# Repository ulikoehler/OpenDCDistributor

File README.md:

# OpenDCDistributor
Open-hardware PCB to distribute DC 12V power to 12V / 5V / 9V &amp; 24V consumers

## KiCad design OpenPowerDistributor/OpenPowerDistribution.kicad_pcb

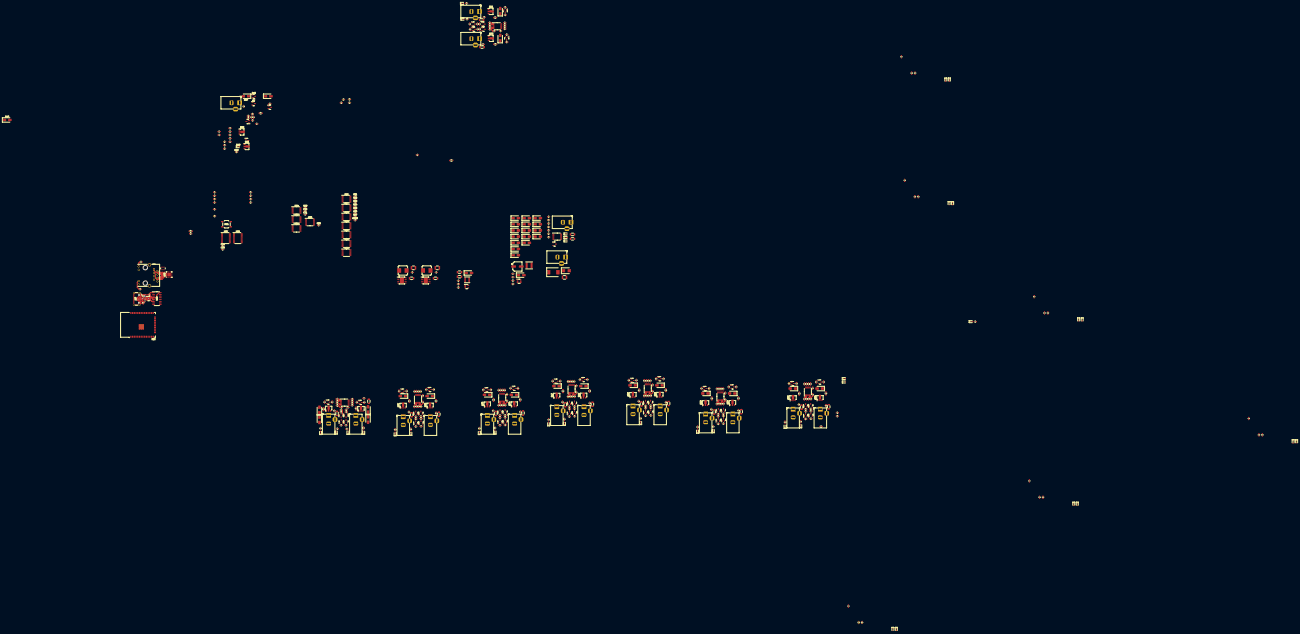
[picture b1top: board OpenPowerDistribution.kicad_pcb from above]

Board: 2 copper layers, 537 parts (0 on the bottom side), 340 nets.

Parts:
C1, C4, C49: 47uF 16V; C_1210_3225Metric
C2, C9, C11, C47: 10uF 50V; C_1206_3216Metric
C3, C12, C13, C16, C17, C18, C21, C22, C23, C26, C27, C28, C31, C32, C33, C36, C37, C38, C41, C42, C43, C46, C48, C51, C52, C55, C56, C57, C60, C72, C73: 100nF 16V; C_0603_1608Metric
C6, C61, C62, C63, C64, C65, C66, C67, C68, C69, C70, C71, C74, C75, C77, C78, C81: 100nF; C_0603_1608Metric
C7: 100pF; C_0603_1608Metric
C8: 47uF 35V; CP_Elec_6.3x5.4
C10, C14, C15, C19, C20, C24, C25, C29, C30, C34, C35, C39, C40, C44, C45, C53, C54, C58, C59: NA; C_0603_1608Metric
C76, C79: 1uF 6.3V; C_0603_1608Metric
D1: SS84C; D_SMC
D2: SMBJ12A; D_SMB
D3: SMAJ3.3A; D_SMA
D4, D7, D8, D15, D15#2, D16, D23, D24, D31, D32, D39, D40, D47, D48, D55, D56, D63, D64, D89, D90: SS36(F); D_SMA
D5, D6, D13, D14, D21, D22, D29, D30, D37, D38, D45, D46, D53, D54, D61, D62, D87, D88: AZ23C16; SOT-23
D9, D11, D17, D19, D25, D27, D33, D35, D41, D43, D49, D51, D57, D59, D65, D67, D91, D93: Red; LED_0603_1608Metric
D10, D12, D18, D20, D26, D28, D34, D36, D42, D44, D50, D52, D58, D60, D66, D68, D92, D94: Green; LED_0603_1608Metric
D69, D70, D71, D72, D73, D74: SMAJ5.0A; D_SMA
D75, D76: SMAJ24A; D_SMA
D77, D78, D79, D80, D81, D82: SMAJ12A; D_SMA
D83, D84, D85, D86: SMAJ9.0A; D_SMA
FB1, FB2, FB3, FB4, FB5, FB6, FB7, FB8, FB9, FB10, FB11, FB12, FB13, FB14, FB15, FB16, FB17, FB18: 220R@100MHz 3A; L_0805_2012Metric
FB19: 200mA 1kR; L_0805_2012Metric
J1, J2, J3, J4, J5, J6, J7, J8, J9, J10, J11, J12, J13, J14, J15, J16, J17, J18, J19: Barrel_Jack; BarrelJack_Horizontal
J20: USB_C_Receptacle_USB2.0; USB_C_Receptacle_HCTL_HC-TYPE-C-16P-01A
J22: RJ45_Hanrun_HR911105A_Horizontal
L1, L4: 3.3uH; L_Bourns_SRP7028A_7.3x6.6mm
L2: 10uH 2A; L_Taiyo-Yuden_NR-50xx
L3: 4.7uH 2A; L_Abracon_ASPI-4030S
Q1, Q2, Q3, Q4, Q7, Q8, Q9, Q10, Q13, Q14, Q15, Q16, Q19, Q20, Q21, Q22, Q25, Q26, Q27, Q28, Q31, Q32, Q33, Q34, Q37, Q38, Q39, Q40, Q43, Q44, Q45, Q46, Q49, Q50, Q51, Q52: BC847; SOT-23
Q5, Q6, Q11, Q12, Q17, Q18, Q23, Q24, Q29, Q30, Q35, Q36, Q41, Q42, Q47, Q48, Q53, Q54: HL20N04; SOT-89-3
R1, R5, R7, R8, R19, R20, R31, R32, R43, R44, R55, R56, R67, R68, R79, R80, R91, R92, R103, R104, R115, R116, R127, R128, R139, R140, R151, R152, R163, R164, R175, R177, R178, R189, R190, R201, R202, R213, R214: 390k; R_0603_1608Metric
R2, R176: 49.9k; R_0603_1608Metric
R3, R225: 220k; R_0603_1608Metric
R4: 68k; R_0603_1608Metric
R6, R9, R10, R33, R34, R57, R58, R81, R82, R105, R106, R129, R130, R153, R154, R179, R180, R203, R204: 15k; R_0603_1608Metric
R11, R12, R25, R26, R35, R36, R49, R50, R59, R60, R73, R74, R83, R84, R97, R98, R107, R108, R121, R122, R131, R132, R145, R146, R155, R156, R169, R170, R181, R182, R195, R196, R205, R206, R219, R220: 100k; R_0603_1608Metric
R13, R14, R15, R17, R37, R38, R39, R41, R61, R62, R63, R65, R85, R86, R87, R89, R109, R110, R111, R113, R133, R134, R135, R137, R157, R158, R159, R161, R183, R184, R185, R187, R207, R208, R209, R211: 1M; R_0603_1608Metric
R16, R18, R40, R42, R64, R66, R88, R90, R112, R114, R136, R138, R160, R162, R186, R188, R210, R212: 33k; R_0603_1608Metric
R21, R22, R45, R46, R69, R70, R93, R94, R117, R118, R141, R142, R165, R166, R191, R192, R215, R216, R226, R229, R230: 10k; R_0603_1608Metric
R23, R24, R47, R48, R71, R72, R95, R96, R119, R120, R143, R144, R167, R168, R193, R194, R217, R218: 33mR; R_1206_3216Metric
R27, R28, R29, R30, R51, R52, R53, R54, R75, R76, R77, R78, R99, R100, R101, R102, R123, R124, R125, R126, R147, R148, R149, R150, R171, R172, R173, R174, R197, R198, R199, R200, R221, R222, R223, R224: 150R; R_0603_1608Metric
R227, R228: 5.1k; R_0603_1608Metric
R231, R233: 12.1k; R_0603_1608Metric
R232, R234: 270R; R_0603_1608Metric
RN1: 49.9R; R_Array_Concave_4x0603
SW1: RST; SW_SPST_TL3342
U1, U13: TPS565208DDA; Texas_HSOP-8-1EP_3.9x4.9mm_P1.27mm
U2: AP63200WU; TSOT-23-6
U3: LGS6302; SOT-23-5
U4, U5, U6, U7, U8, U9, U10, U11, U12: LM324; TSSOP-14_4.4x5mm_P0.65mm
U14: USBLC6-2SC6; SOT-23-6
U15: ESP32-WROOM-32; ESP32-WROOM-32D
U16, U17, U18, U19, U20, U21, U22: 74HCT595; TSSOP-16_4.4x5mm_P0.65mm
U23, U24, U25, U26: 74HC165; TSSOP-16_4.4x5mm_P0.65mm
U27, U28: CD4067BMT/TR; TSSOP-24_4.4x7.8mm_P0.65mm
U29: CH340C; SOIC-16_3.9x9.9mm_P1.27mm
U30: LAN8720A; QFN-24-1EP_4x4mm_P0.5mm_EP2.6x2.6mm

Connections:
+3.3V: C7.1, C8.1, C61.2, C62.2, C63.2, C64.2, C65.2, C66.2, C67.2, C68.2, C69.2, C70.2, C71.2, C74.2, C75.1, D3.1 (A1), FB19.2, L2.2, R3.1, R225.1, R226.1, R229.1, R232.2, U15.2 (VDD), U16.10 (~SRCLR), U16.16 (VCC), U17.10 (~SRCLR), U17.16 (VCC), U18.10 (~SRCLR), U18.16 (VCC), U19.10 (~SRCLR), U19.16 (VCC), U20.10 (~SRCLR), U20.16 (VCC), U21.10 (~SRCLR), U21.16 (VCC), U22.10 (~SRCLR), U22.16 (VCC), U23.16 (VCC), U24.16 (VCC), U25.16 (VCC), U26.16 (VCC), U29.4 (V3), U29.16 (VCC), U30.9 (VDDIO)
+3.3VPHY: C77.2, C78.2, C79.2, C81.2, FB19.1, J22.4 (TCT), J22.5 (RCT), RN1.5 (R4.2), RN1.6 (R3.2), RN1.7 (R2.2), RN1.8 (R1.2), U30.1 (VDD2A), U30.19 (VDD1A)
+3V3: C72.1, C73.1, R9.1, R10.1, R27.2, R28.2, R29.2, R30.2, R33.1, R34.1, R51.2, R52.2, R53.2, R54.2, R57.1, R58.1, R75.2, R76.2, R77.2, R78.2, R81.1, R82.1, R99.2, R100.2, R101.2, R102.2, R105.1, R106.1, R123.2, R124.2, R125.2, R126.2, R129.1, R130.1, R147.2, R148.2, R149.2, R150.2, R153.1, R154.1, R171.2, R172.2, R173.2, R174.2, R179.1, R180.1, R197.2, R198.2, R199.2, R200.2, R203.1, R204.1, R221.2, R222.2, R223.2, R224.2, U27.24 (VCC), U28.24 (VCC)
+5V: C4.2, D7.2 (A), D8.2 (A), D15.2 (A), D15#2.2 (A), D16.2 (A), D23.2 (A), D24.2 (A), L1.2, R1.1, U3.4 (EN)
+9V: C49.2, D63.2 (A), D64.2 (A), D89.2 (A), D90.2 (A), L4.2, R175.1
+12V: C1.2, C9.2, C16.1, C21.1, C26.1, C31.1, C36.1, C41.1, C46.1, C55.1, C60.1, D1.1 (K), D2.1 (A1), D31.2 (A), D32.2 (A), D39.2 (A), D40.2 (A), D47.2 (A), D48.2 (A), L3.1, U1.1 (EN), U1.8 (VIN), U2.2 (EN), U2.3 (IN), U3.5 (IN), U4.4 (V+), U5.4 (V+), U6.4 (V+), U7.4 (V+), U8.4 (V+), U9.4 (V+), U10.4 (V+), U11.4 (V+), U12.4 (V+), U13.1 (EN), U13.8 (VIN)
+24V: D55.2 (A), D56.2 (A)
+30V: C10.1, C11.2, D4.1 (K), R5.1, R15.1, R17.1, R39.1, R41.1, R63.1, R65.1, R87.1, R89.1, R111.1, R113.1, R135.1, R137.1, R159.1, R161.1, R185.1, R187.1, R209.1, R211.1
/Analog multiplexer/AMUX-Out: U27.1 (COM), U28.1 (COM)
/Analog multiplexer/AMUX.A0: U27.10 (S0), U28.10 (S0)
/Analog multiplexer/AMUX.A1: U27.11 (S1), U28.11 (S1)
/Analog multiplexer/AMUX.A2: U27.14 (S2), U28.14 (S2)
/Analog multiplexer/AMUX.A3: U27.13 (S3), U28.13 (S3)
/DC Output channels/5V output #1/O1+: D5.2 (K), D69.1 (A1), J2.1, Q5.3 (S), R25.1
/DC Output channels/5V output #1/O1-: D69.2 (A2), J2.2, R23.1, R25.2, U4.5 (+)
/DC Output channels/5V output #1/O2+: D6.2 (K), D70.1 (A1), J3.1, Q6.3 (S), R26.1
/DC Output channels/5V output #1/O2-: D70.2 (A2), J3.2, R24.1, R26.2, U4.12 (+)
/DC Output channels/5V output #2/O1+: D13.2 (K), D71.1 (A1), J4.1, Q11.3 (S), R49.1
/DC Output channels/5V output #2/O1-: D71.2 (A2), J4.2, R47.1, R49.2, U8.5 (+)
/DC Output channels/5V output #2/O2+: D14.2 (K), D72.1 (A1), J5.1, Q12.3 (S), R50.1
/DC Output channels/5V output #2/O2-: D72.2 (A2), J5.2, R48.1, R50.2, U8.12 (+)
/DC Output channels/5V output #3/O1+: D21.2 (K), D73.1 (A1), J6.1, Q17.3 (S), R73.1
/DC Output channels/5V output #3/O1-: D73.2 (A2), J6.2, R71.1, R73.2, U9.5 (+)
/DC Output channels/5V output #3/O2+: D22.2 (K), D74.1 (A1), J7.1, Q18.3 (S), R74.1
/DC Output channels/5V output #3/O2-: D74.2 (A2), J7.2, R72.1, R74.2, U9.12 (+)
/DC Output channels/9V output #1/O1+: D61.2 (K), D83.1 (A1), J16.1, Q47.3 (S), R195.1
/DC Output channels/9V output #1/O1-: D83.2 (A2), J16.2, R193.1, R195.2, U6.5 (+)
/DC Output channels/9V output #1/O2+: D62.2 (K), D84.1 (A1), J17.1, Q48.3 (S), R196.1
/DC Output channels/9V output #1/O2-: D84.2 (A2), J17.2, R194.1, R196.2, U6.12 (+)
/DC Output channels/9V output #2/O1+: D85.1 (A1), D87.2 (K), J18.1, Q53.3 (S), R219.1
/DC Output channels/9V output #2/O1-: D85.2 (A2), J18.2, R217.1, R219.2, U7.5 (+)
/DC Output channels/9V output #2/O2+: D86.1 (A1), D88.2 (K), J19.1, Q54.3 (S), R220.1
/DC Output channels/9V output #2/O2-: D86.2 (A2), J19.2, R218.1, R220.2, U7.12 (+)
/DC Output channels/12V output #1/O1+: D29.2 (K), D77.1 (A1), J8.1, Q23.3 (S), R97.1
/DC Output channels/12V output #1/O1-: D77.2 (A2), J8.2, R95.1, R97.2, U10.5 (+)
/DC Output channels/12V output #1/O2+: D30.2 (K), D78.1 (A1), J9.1, Q24.3 (S), R98.1
/DC Output channels/12V output #1/O2-: D78.2 (A2), J9.2, R96.1, R98.2, U10.12 (+)
/DC Output channels/12V output #2/O1+: D37.2 (K), D79.1 (A1), J10.1, Q29.3 (S), R121.1
/DC Output channels/12V output #2/O1-: D79.2 (A2), J10.2, R119.1, R121.2, U11.5 (+)
/DC Output channels/12V output #2/O2+: D38.2 (K), D80.1 (A1), J11.1, Q30.3 (S), R122.1
/DC Output channels/12V output #2/O2-: D80.2 (A2), J11.2, R120.1, R122.2, U11.12 (+)
/DC Output channels/12V output #3/O1+: D45.2 (K), D81.1 (A1), J12.1, Q35.3 (S), R145.1
/DC Output channels/12V output #3/O1-: D81.2 (A2), J12.2, R143.1, R145.2, U5.5 (+)
/DC Output channels/12V output #3/O2+: D46.2 (K), D82.1 (A1), J13.1, Q36.3 (S), R146.1
/DC Output channels/12V output #3/O2-: D82.2 (A2), J13.2, R144.1, R146.2, U5.12 (+)
/DC Output channels/24V output #1/O1+: D53.2 (K), D75.1 (A1), J14.1, Q41.3 (S), R169.1
/DC Output channels/24V output #1/O1-: D75.2 (A2), J14.2, R167.1, R169.2, U12.5 (+)
/DC Output channels/24V output #1/O2+: D54.2 (K), D76.1 (A1), J15.1, Q42.3 (S), R170.1
/DC Output channels/24V output #1/O2-: D76.2 (A2), J15.2, R168.1, R170.2, U12.12 (+)
/DC Output channels/A_{In}1: C14.2, R19.1, U4.3 (+), U4.7
/DC Output channels/A_{In}2: C15.2, R20.1, U4.9 (-), U4.14
/DC Output channels/A_{In}3: C19.2, R43.1, U8.3 (+), U8.7
/DC Output channels/A_{In}4: C20.2, R44.1, U8.9 (-), U8.14
/DC Output channels/A_{In}5: C24.2, R67.1, U9.3 (+), U9.7
/DC Output channels/A_{In}6: C25.2, R68.1, U9.9 (-), U9.14
/DC Output channels/A_{In}7: C44.2, R163.1, U12.3 (+), U12.7
/DC Output channels/A_{In}8: C45.2, R164.1, U12.9 (-), U12.14
/DC Output channels/A_{In}9: C29.2, R91.1, U10.3 (+), U10.7
/DC Output channels/A_{In}10: C30.2, R92.1, U10.9 (-), U10.14
/DC Output channels/A_{In}11: C34.2, R115.1, U11.3 (+), U11.7
/DC Output channels/A_{In}12: C35.2, R116.1, U11.9 (-), U11.14
/DC Output channels/A_{In}13: C39.2, R139.1, U5.3 (+), U5.7
/DC Output channels/A_{In}14: C40.2, R140.1, U5.9 (-), U5.14
/DC Output channels/A_{In}15: C53.2, R189.1, U6.3 (+), U6.7
/DC Output channels/A_{In}16: C54.2, R190.1, U6.9 (-), U6.14
/DC Output channels/A_{In}17: C58.2, R213.1, U7.3 (+), U7.7
/DC Output channels/A_{In}18: C59.2, R214.1, U7.9 (-), U7.14
/DC Output channels/D_{In}1: Q1.3 (C), R9.2, U23.12 (D1)
/DC Output channels/D_{In}2: Q2.3 (C), R10.2, U23.13 (D2)
/DC Output channels/D_{In}3: Q7.3 (C), R33.2, U23.14 (D3)
/DC Output channels/D_{In}4: Q8.3 (C), R34.2, U23.3 (D4)
/DC Output channels/D_{In}5: Q13.3 (C), R57.2, U23.4 (D5)
/DC Output channels/D_{In}6: Q14.3 (C), R58.2, U23.5 (D6)
/DC Output channels/D_{In}7: Q37.3 (C), R153.2, U23.6 (D7)
/DC Output channels/D_{In}8: Q38.3 (C), R154.2, U24.11 (D0), U25.11 (D0)
/DC Output channels/D_{In}9: Q19.3 (C), R81.2, U24.12 (D1), U25.12 (D1)
/DC Output channels/D_{In}10: Q20.3 (C), R82.2, U24.13 (D2), U25.13 (D2)
/DC Output channels/D_{In}11: Q25.3 (C), R105.2, U24.14 (D3), U25.14 (D3)
/DC Output channels/D_{In}12: Q26.3 (C), R106.2, U24.3 (D4), U25.3 (D4)
/DC Output channels/D_{In}13: Q31.3 (C), R129.2, U24.4 (D5), U25.4 (D5)
/DC Output channels/D_{In}14: Q32.3 (C), R130.2, U24.5 (D6), U25.5 (D6)
/DC Output channels/D_{In}15: Q43.3 (C), R179.2, U24.6 (D7), U25.6 (D7)
/DC Output channels/D_{In}16: Q44.3 (C), R180.2, U26.11 (D0)
/DC Output channels/D_{In}17: Q49.3 (C), R203.2, U26.12 (D1)
/DC Output channels/D_{In}18: Q50.3 (C), R204.2, U26.13 (D2)
/Input multiplexer/SCLK: U16.11 (SRCLK), U17.11 (SRCLK), U18.11 (SRCLK), U19.11 (SRCLK), U20.11 (SRCLK), U21.11 (SRCLK), U22.11 (SRCLK), U23.2 (CP), U24.2 (CP), U25.2 (CP), U26.2 (CP)
/Input multiplexer/~LOAD: U16.12 (RCLK), U17.12 (RCLK), U18.12 (RCLK), U19.12 (RCLK), U20.12 (RCLK), U21.12 (RCLK), U22.12 (RCLK), U23.1 (~PL), U24.1 (~PL), U25.1 (~PL), U26.1 (~PL)
/MCU/DO4: R231.1, U15.14 (IO12)
/MCU/ESP32-RMII-CRSDV: U15.12 (IO27), U30.11 (CRS_DV/MODE2)
/MCU/ESP32-RMII-MDC: U15.37 (IO23), U30.13 (MDC)
/MCU/ESP32-RMII-MDIO: U15.30 (IO18), U30.12 (MDIO)
/MCU/ESP32-RMII-REFCLKOUT: U15.28 (IO17), U30.5 (XTAL1/CLKIN)
/MCU/ESP32-RMII-RXD0: U15.10 (IO25), U30.8 (RXD0/MODE0)
/MCU/ESP32-RMII-RXD1: U15.11 (IO26), U30.7 (RXD1/MODE1)
/MCU/ESP32-RMII-TX-EN: U15.33 (IO21), U30.16 (TXEN)
/MCU/ESP32-RMII-TXD0: U15.31 (IO19), U30.17 (TXD0)
/MCU/ESP32-RMII-TXD1: U15.36 (IO22), U30.18 (TXD1)
/MCU/Ethernet/1.2VPHY: C76.2, U30.6 (VDDCR)
/MCU/Ethernet/LED-Green: J22.10, U30.2 (LED2/nINTSEL)
/MCU/Ethernet/LED-Yellow: J22.12, U30.3 (LED1/REGOFF)
/MCU/Ethernet/PHY-RXN: J22.6 (RD-), RN1.4 (R4.1), U30.22 (RXN)
/MCU/Ethernet/PHY-RXP: J22.3 (RD+), RN1.3 (R3.1), U30.23 (RXP)
/MCU/Ethernet/PHY-TXN: J22.2 (TD-), RN1.2 (R2.1), U30.20 (TXN)
/MCU/Ethernet/PHY-TXP: J22.1 (TD+), RN1.1 (R1.1), U30.21 (TXP)
/Output multiplexer/~OE: R225.2, U16.13 (~OE), U17.13 (~OE), U18.13 (~OE), U19.13 (~OE), U20.13 (~OE), U21.13 (~OE), U22.13 (~OE)
/USB/USB-D+: J20.A6 (D+), J20.B6 (D+), U14.1 (I/O1), U14.6 (I/O1), U29.5 (UD+)
/USB/USB-D-: J20.A7 (D-), J20.B7 (D-), U14.3 (I/O2), U14.4 (I/O2), U29.6 (UD-)
ESP32-BOOT: R229.2, U15.25 (IO0), U29.14 (~RTS)
ESP32-UART-RX: U15.34 (RXD0/IO3), U29.2 (TXD)
ESP32-UART-TX: U15.35 (TXD0/IO1), U29.3 (RXD)
ESP32-~RST: R226.2, SW1.2, U15.3 (EN), U29.13 (~DTR), U30.15 (RST)
GND: C1.1, C2.1, C4.1, C8.2, C9.1, C11.1, C16.2, C21.2, C26.2, C31.2, C36.2, C41.2, C46.2, C47.1, C49.1, C55.2, C60.2, C61.1, C62.1, C63.1, C64.1, C65.1, C66.1, C67.1, C68.1, C69.1, C70.1, C71.1, C72.2, C73.2, C74.1, C75.2, C76.1, C77.1, C78.1, C79.1, C81.1, D2.2 (A2), D3.2 (A2), J1.2, J20.A1 (GND), J20.A12 (GND), J20.B1 (GND), J20.B12 (GND), J20.S1 (SHIELD), J22.8, J22.SH, Q1.2 (E), Q2.2 (E), Q3.2 (E), Q4.2 (E), Q7.2 (E), Q8.2 (E), Q9.2 (E), Q10.2 (E), Q13.2 (E), Q14.2 (E), Q15.2 (E), Q16.2 (E), Q19.2 (E), Q20.2 (E), Q21.2 (E), Q22.2 (E), Q25.2 (E), Q26.2 (E), Q27.2 (E), Q28.2 (E), Q31.2 (E), Q32.2 (E), Q33.2 (E), Q34.2 (E), Q37.2 (E), Q38.2 (E), Q39.2 (E), Q40.2 (E), Q43.2 (E), Q44.2 (E), Q45.2 (E), Q46.2 (E), Q49.2 (E), Q50.2 (E), Q51.2 (E), Q52.2 (E), R2.2, R4.2, R6.2, R21.1, R22.1, R23.2, R24.2, R45.1, R46.1, R47.2, R48.2, R69.1, R70.1, R71.2, R72.2, R93.1, R94.1, R95.2, R96.2, R117.1, R118.1, R119.2, R120.2, R141.1, R142.1, R143.2, R144.2, R165.1, R166.1, R167.2, R168.2, R176.2, R191.1, R192.1, R193.2, R194.2, R215.1, R216.1, R217.2, R218.2, R227.1, R228.1, R230.1, R231.2, R233.2, R234.2, SW1.1, U1.5 (GND), U1.9 (EP), U2.4 (GND), U3.2 (GND), U4.11 (V-), U5.11 (V-), U6.11 (V-), U7.11 (V-), U8.11 (V-), U9.11 (V-), U10.11 (V-), U11.11 (V-), U12.11 (V-), U13.5 (GND), U13.9 (EP), U14.2 (GND), U15.1 (GND), U15.15 (GND), U15.38 (GND), U15.39 (GND), U16.8 (GND), U17.8 (GND), U18.8 (GND), U19.8 (GND), U20.8 (GND), U21.8 (GND), U22.8 (GND), U23.8 (GND), U23.15 (~CE), U24.8 (GND), U24.15 (~CE), U25.8 (GND), U25.15 (~CE), U26.8 (GND), U26.15 (~CE), U27.12 (GND), U28.12 (GND), U29.1 (GND), U30.25 (VSS)
unnamed: C12.2, R12.2, R13.1, U4.1
unnamed: C13.2, R11.2, R14.1, U4.8
unnamed: C17.2, R36.2, R37.1, U8.1
unnamed: C18.2, R35.2, R38.1, U8.8
unnamed: C22.2, R60.2, R61.1, U9.1
unnamed: C23.2, R59.2, R62.1, U9.8
unnamed: C27.2, R84.2, R85.1, U10.1
unnamed: C28.2, R83.2, R86.1, U10.8
unnamed: C32.2, R108.2, R109.1, U11.1
unnamed: C33.2, R107.2, R110.1, U11.8
unnamed: C37.2, R132.2, R133.1, U5.1
unnamed: C38.2, R131.2, R134.1, U5.8
unnamed: C42.2, R156.2, R157.1, U12.1
unnamed: C43.2, R155.2, R158.1, U12.8
unnamed: C51.2, R182.2, R183.1, U6.1
unnamed: C52.2, R181.2, R184.1, U6.8
unnamed: C56.2, R206.2, R207.1, U7.1
unnamed: C57.2, R205.2, R208.1, U7.8
unnamed: D1.2 (A), J1.1
unnamed: D4.2 (A), L3.2, U3.1 (SW)
unnamed: D7.1 (K), FB1.1
unnamed: D8.1 (K), FB10.1
unnamed: D9.2 (A), R27.1
unnamed: D10.2 (A), R28.1
unnamed: D11.2 (A), R29.1
unnamed: D12.2 (A), R30.1
unnamed: D15.1 (K), D15#2.1 (K), FB2.1
unnamed: D16.1 (K), FB11.1
unnamed: D17.2 (A), R51.1
unnamed: D18.2 (A), R52.1
unnamed: D19.2 (A), R53.1
unnamed: D20.2 (A), R54.1
unnamed: D23.1 (K), FB3.1
unnamed: D24.1 (K), FB12.1
unnamed: D25.2 (A), R75.1
unnamed: D26.2 (A), R76.1
unnamed: D27.2 (A), R77.1
unnamed: D28.2 (A), R78.1
unnamed: D31.1 (K), FB4.1
unnamed: D32.1 (K), FB13.1
unnamed: D33.2 (A), R99.1
unnamed: D34.2 (A), R100.1
unnamed: D35.2 (A), R101.1
unnamed: D36.2 (A), R102.1
unnamed: D39.1 (K), FB5.1
unnamed: D40.1 (K), FB14.1
unnamed: D41.2 (A), R123.1
unnamed: D42.2 (A), R124.1
unnamed: D43.2 (A), R125.1
unnamed: D44.2 (A), R126.1
unnamed: D47.1 (K), FB6.1
unnamed: D48.1 (K), FB15.1
unnamed: D49.2 (A), R147.1
unnamed: D50.2 (A), R148.1
unnamed: D51.2 (A), R149.1
unnamed: D52.2 (A), R150.1
unnamed: D55.1 (K), FB7.1
unnamed: D56.1 (K), FB16.1
unnamed: D57.2 (A), R171.1
unnamed: D58.2 (A), R172.1
unnamed: D59.2 (A), R173.1
unnamed: D60.2 (A), R174.1
unnamed: D63.1 (K), FB8.1
unnamed: D64.1 (K), FB17.1
unnamed: D65.2 (A), R197.1
unnamed: D66.2 (A), R198.1
unnamed: D67.2 (A), R199.1
unnamed: D68.2 (A), R200.1
unnamed: D89.1 (K), FB9.1
unnamed: D90.1 (K), FB18.1
unnamed: D91.2 (A), R221.1
unnamed: D92.2 (A), R222.1
unnamed: D93.2 (A), R223.1
unnamed: D94.2 (A), R224.1
unnamed: J20.A5 (CC1), R227.2
unnamed: J20.B5 (CC2), R228.2
unnamed: J22.9, R232.1
unnamed: J22.11, R234.1
unnamed: Q1.1 (B), R12.1
unnamed: Q2.1 (B), R11.1
unnamed: Q3.1 (B), R13.2
unnamed: Q3.3 (C), R16.2
unnamed: Q4.1 (B), R14.2
unnamed: Q4.3 (C), R18.2
unnamed: FB1.2, Q5.2 (D)
unnamed: D5.1 (K), Q5.1 (G), R15.2, R16.1
unnamed: FB10.2, Q6.2 (D)
unnamed: D6.1 (K), Q6.1 (G), R17.2, R18.1
unnamed: Q7.1 (B), R36.1
unnamed: Q8.1 (B), R35.1
unnamed: Q9.1 (B), R37.2
unnamed: Q9.3 (C), R40.2
unnamed: Q10.1 (B), R38.2
unnamed: Q10.3 (C), R42.2
unnamed: FB2.2, Q11.2 (D)
unnamed: D13.1 (K), Q11.1 (G), R39.2, R40.1
unnamed: FB11.2, Q12.2 (D)
unnamed: D14.1 (K), Q12.1 (G), R41.2, R42.1
unnamed: Q13.1 (B), R60.1
unnamed: Q14.1 (B), R59.1
unnamed: Q15.1 (B), R61.2
unnamed: Q15.3 (C), R64.2
unnamed: Q16.1 (B), R62.2
unnamed: Q16.3 (C), R66.2
unnamed: FB3.2, Q17.2 (D)
unnamed: D21.1 (K), Q17.1 (G), R63.2, R64.1
unnamed: FB12.2, Q18.2 (D)
unnamed: D22.1 (K), Q18.1 (G), R65.2, R66.1
unnamed: Q19.1 (B), R84.1
unnamed: Q20.1 (B), R83.1
unnamed: Q21.1 (B), R85.2
unnamed: Q21.3 (C), R88.2
unnamed: Q22.1 (B), R86.2
unnamed: Q22.3 (C), R90.2
unnamed: FB4.2, Q23.2 (D)
unnamed: D29.1 (K), Q23.1 (G), R87.2, R88.1
unnamed: FB13.2, Q24.2 (D)
unnamed: D30.1 (K), Q24.1 (G), R89.2, R90.1
unnamed: Q25.1 (B), R108.1
unnamed: Q26.1 (B), R107.1
unnamed: Q27.1 (B), R109.2
unnamed: Q27.3 (C), R112.2
unnamed: Q28.1 (B), R110.2
unnamed: Q28.3 (C), R114.2
unnamed: FB5.2, Q29.2 (D)
unnamed: D37.1 (K), Q29.1 (G), R111.2, R112.1
unnamed: FB14.2, Q30.2 (D)
unnamed: D38.1 (K), Q30.1 (G), R113.2, R114.1
unnamed: Q31.1 (B), R132.1
unnamed: Q32.1 (B), R131.1
unnamed: Q33.1 (B), R133.2
unnamed: Q33.3 (C), R136.2
unnamed: Q34.1 (B), R134.2
unnamed: Q34.3 (C), R138.2
unnamed: FB6.2, Q35.2 (D)
unnamed: D45.1 (K), Q35.1 (G), R135.2, R136.1
unnamed: FB15.2, Q36.2 (D)
unnamed: D46.1 (K), Q36.1 (G), R137.2, R138.1
unnamed: Q37.1 (B), R156.1
unnamed: Q38.1 (B), R155.1
unnamed: Q39.1 (B), R157.2
unnamed: Q39.3 (C), R160.2
unnamed: Q40.1 (B), R158.2
unnamed: Q40.3 (C), R162.2
unnamed: FB7.2, Q41.2 (D)
unnamed: D53.1 (K), Q41.1 (G), R159.2, R160.1
unnamed: FB16.2, Q42.2 (D)
unnamed: D54.1 (K), Q42.1 (G), R161.2, R162.1
unnamed: Q43.1 (B), R182.1
unnamed: Q44.1 (B), R181.1
unnamed: Q45.1 (B), R183.2
unnamed: Q45.3 (C), R186.2
unnamed: Q46.1 (B), R184.2
unnamed: Q46.3 (C), R188.2
unnamed: FB8.2, Q47.2 (D)
unnamed: D61.1 (K), Q47.1 (G), R185.2, R186.1
unnamed: FB17.2, Q48.2 (D)
unnamed: D62.1 (K), Q48.1 (G), R187.2, R188.1
unnamed: Q49.1 (B), R206.1
unnamed: Q50.1 (B), R205.1
unnamed: Q51.1 (B), R207.2
unnamed: Q51.3 (C), R210.2
unnamed: Q52.1 (B), R208.2
unnamed: Q52.3 (C), R212.2
unnamed: FB9.2, Q53.2 (D)
unnamed: D87.1 (K), Q53.1 (G), R209.2, R210.1
unnamed: FB18.2, Q54.2 (D)
unnamed: D88.1 (K), Q54.1 (G), R211.2, R212.1
unnamed: C3.2, L1.1, U1.6 (SW)
unnamed: C3.1, U1.7 (VBST)
unnamed: R1.2, R2.1, U1.2 (VFB)
unnamed: C2.2, U1.3 (VREG5)
unnamed: C6.2, U2.6 (BST)
unnamed: C7.2, R3.2, R4.1, U2.1 (FB)
unnamed: C6.1, L2.1, U2.5 (SW)
unnamed: C10.2, R5.2, R6.1, U3.3 (FB)
unnamed: C12.1, R7.2, U4.2 (-)
unnamed: C14.1, R19.2, R21.2, U4.6 (-)
unnamed: C13.1, R8.2, U4.10 (+)
unnamed: C15.1, R20.2, R22.2, U4.13 (-)
unnamed: C37.1, R127.2, U5.2 (-)
unnamed: C39.1, R139.2, R141.2, U5.6 (-)
unnamed: C38.1, R128.2, U5.10 (+)
unnamed: C40.1, R140.2, R142.2, U5.13 (-)
unnamed: C51.1, R177.2, U6.2 (-)
unnamed: C53.1, R189.2, R191.2, U6.6 (-)
unnamed: C52.1, R178.2, U6.10 (+)
unnamed: C54.1, R190.2, R192.2, U6.13 (-)
unnamed: C56.1, R201.2, U7.2 (-)
unnamed: C58.1, R213.2, R215.2, U7.6 (-)
unnamed: C57.1, R202.2, U7.10 (+)
unnamed: C59.1, R214.2, R216.2, U7.13 (-)
unnamed: C17.1, R31.2, U8.2 (-)
unnamed: C19.1, R43.2, R45.2, U8.6 (-)
unnamed: C18.1, R32.2, U8.10 (+)
unnamed: C20.1, R44.2, R46.2, U8.13 (-)
unnamed: C22.1, R55.2, U9.2 (-)
unnamed: C24.1, R67.2, R69.2, U9.6 (-)
unnamed: C23.1, R56.2, U9.10 (+)
unnamed: C25.1, R68.2, R70.2, U9.13 (-)
unnamed: C27.1, R79.2, U10.2 (-)
unnamed: C29.1, R91.2, R93.2, U10.6 (-)
unnamed: C28.1, R80.2, U10.10 (+)
unnamed: C30.1, R92.2, R94.2, U10.13 (-)
unnamed: C32.1, R103.2, U11.2 (-)
unnamed: C34.1, R115.2, R117.2, U11.6 (-)
unnamed: C33.1, R104.2, U11.10 (+)
unnamed: C35.1, R116.2, R118.2, U11.13 (-)
unnamed: C42.1, R151.2, U12.2 (-)
unnamed: C44.1, R163.2, R165.2, U12.6 (-)
unnamed: C43.1, R152.2, U12.10 (+)
unnamed: C45.1, R164.2, R166.2, U12.13 (-)
unnamed: C48.2, L4.1, U13.6 (SW)
unnamed: C48.1, U13.7 (VBST)
unnamed: R175.2, R176.1, U13.2 (VFB)
unnamed: C47.2, U13.3 (VREG5)
unnamed: R230.2, U15.24 (IO2)
unnamed: U16.9 (QH'), U17.14 (SER)
unnamed: U17.9 (QH'), U18.14 (SER)
unnamed: U18.9 (QH'), U19.14 (SER)
unnamed: U19.9 (QH'), U20.14 (SER)
unnamed: U20.9 (QH'), U21.14 (SER)
unnamed: U21.9 (QH'), U22.14 (SER)
unnamed: U23.9 (Q7), U24.10 (DS)
unnamed: U24.9 (Q7), U25.10 (DS)
unnamed: U25.9 (Q7), U26.10 (DS)
unnamed: R233.1, U30.24 (RBIAS)
VUSB: J20.A4 (VBUS), J20.A9 (VBUS), J20.B4 (VBUS), J20.B9 (VBUS), U14.5 (VBUS)

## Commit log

2023-09-16 Initialize KiCAD project
2023-09-17 Started to draw schematic
2023-09-17 Added manual high side power switch
2023-09-17 More schematic progress
2023-09-17 Added LEDs
2023-09-18 More work on schematic wiring
2023-09-18 Start to make layout
2023-09-18 Analog multiplexer work
2023-09-23 Work mostly on Ethernet schematic
